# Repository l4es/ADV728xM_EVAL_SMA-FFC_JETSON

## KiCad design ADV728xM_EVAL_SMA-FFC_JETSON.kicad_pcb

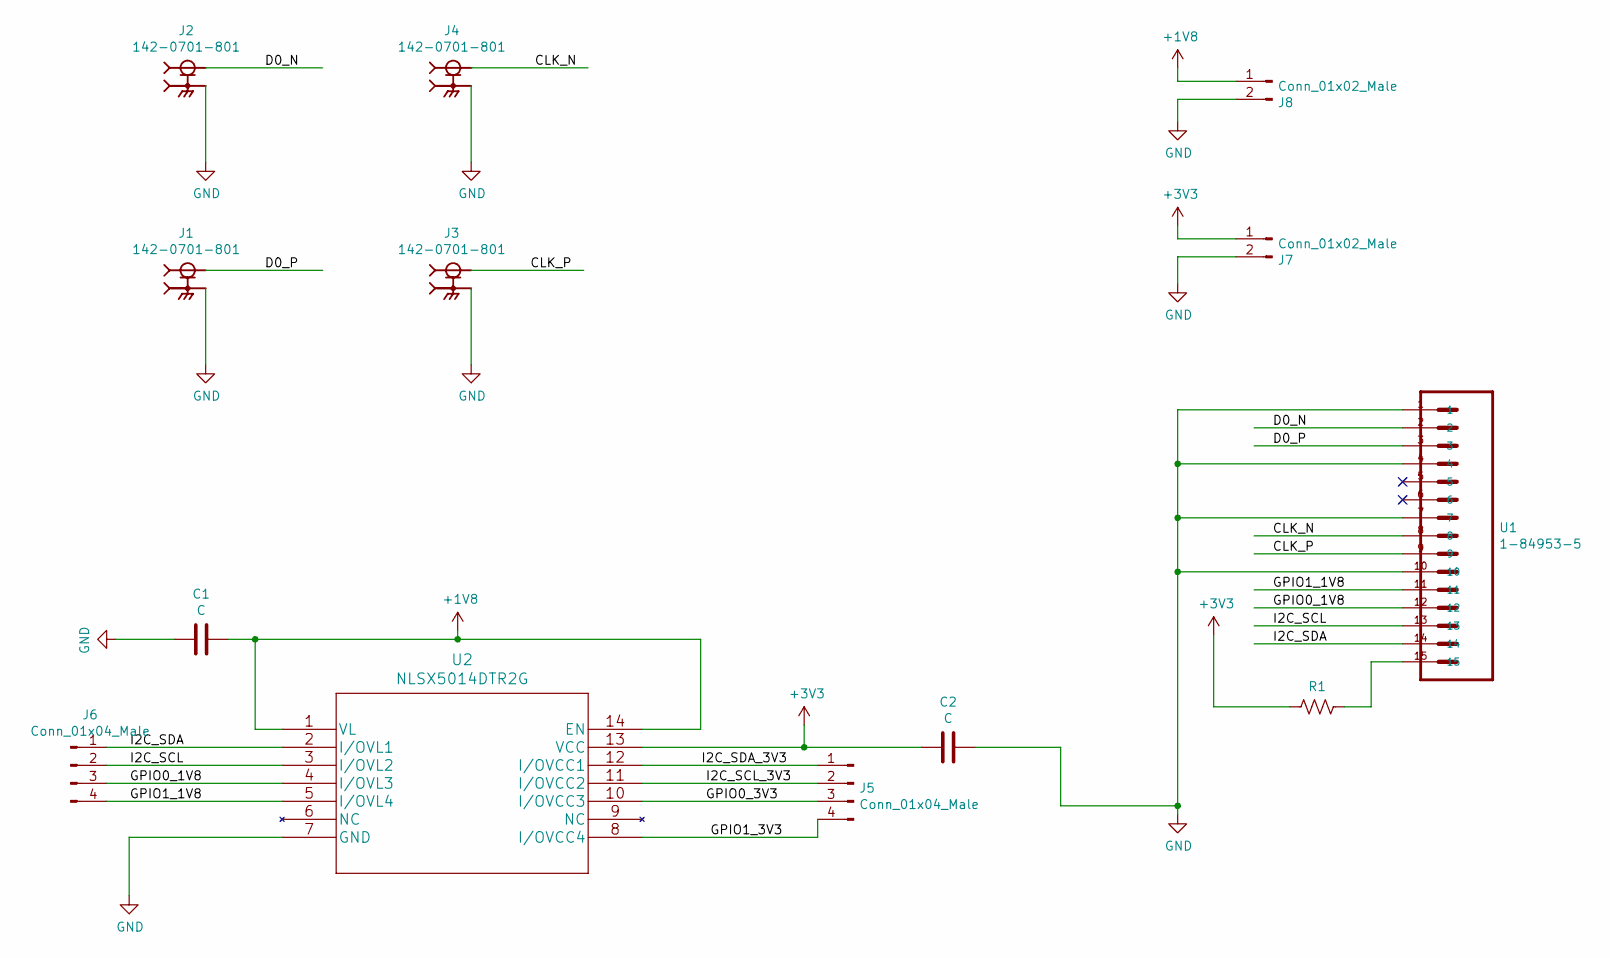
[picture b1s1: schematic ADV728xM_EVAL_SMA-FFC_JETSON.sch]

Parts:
C1, C2: C; C_0603_1608Metric_Pad1.08x0.95mm_HandSolder
J1, J2, J3, J4: 142-0701-801; CINCH_142-0701-801; PARTREV N/A
J5, J6: Conn_01x04_Male; PinHeader_1x04_P2.54mm_Vertical
J7, J8: Conn_01x02_Male; PinHeader_1x02_P2.54mm_Vertical
R1: 0; R_0805_2012Metric_Pad1.20x1.40mm_HandSolder
U1: 1-84953-5; TE_1-84953-5
U2: NLSX5014DTR2G

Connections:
+1V8: C1.2, J8.1, U2.1 (VL), U2.14 (EN)
+3V3: C2.2, J7.1, R1.2, U2.13 (VCC)
/CLK_N: J4.1, U1.8
/CLK_P: J3.1, U1.9
/D0_N: J2.1, U1.2
/D0_P: J1.1, U1.3
/GPIO0_1V8: J6.3, U1.12, U2.4 (I/OVL3)
/GPIO0_3V3: J5.3, U2.10 (I/OVCC3)
/GPIO1_1V8: J6.4, U1.11, U2.5 (I/OVL4)
/GPIO1_3V3: J5.4, U2.8 (I/OVCC4)
/I2C_SCL: J6.2, U1.13, U2.3 (I/OVL2)
/I2C_SCL_3V3: J5.2, U2.11 (I/OVCC2)
/I2C_SDA: J6.1, U1.14, U2.2 (I/OVL1)
/I2C_SDA_3V3: J5.1, U2.12 (I/OVCC1)
GND: C1.1, C2.1, J1.S1, J1.S2, J1.S3, J1.S4, J2.S1, J2.S2, J2.S3, J2.S4, J3.S1, J3.S2, J3.S3, J3.S4, J4.S1, J4.S2, J4.S3, J4.S4, J7.2, J8.2, U1.1, U1.4, U1.7, U1.10, U2.7 (GND)
unnamed: R1.1, U1.15

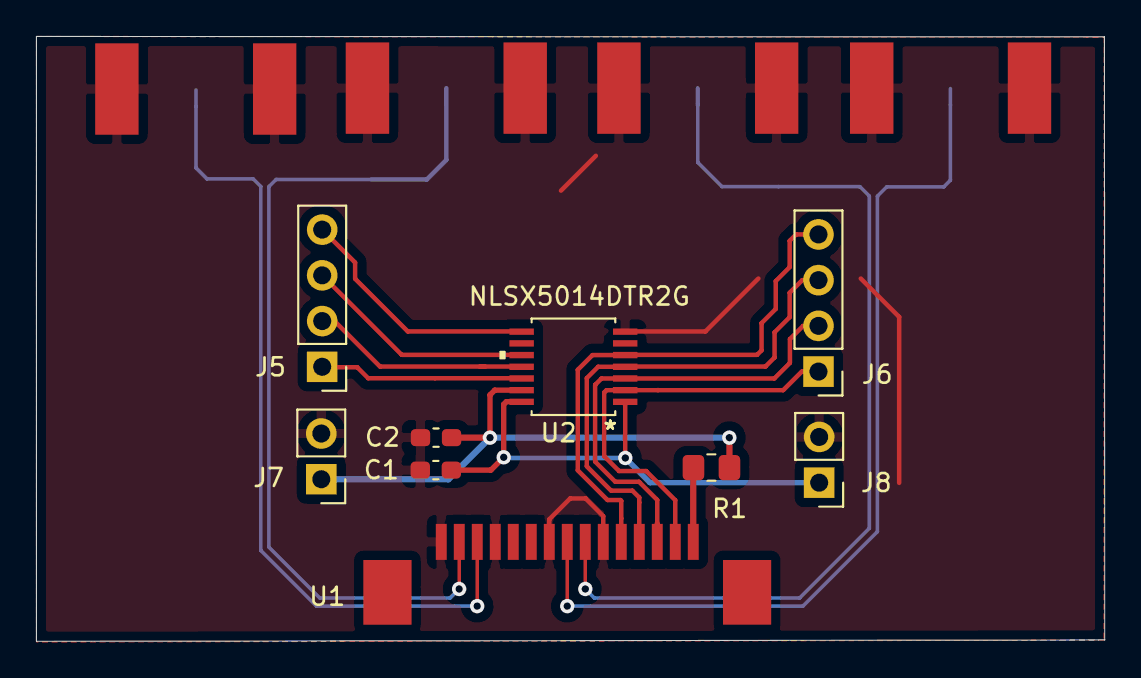
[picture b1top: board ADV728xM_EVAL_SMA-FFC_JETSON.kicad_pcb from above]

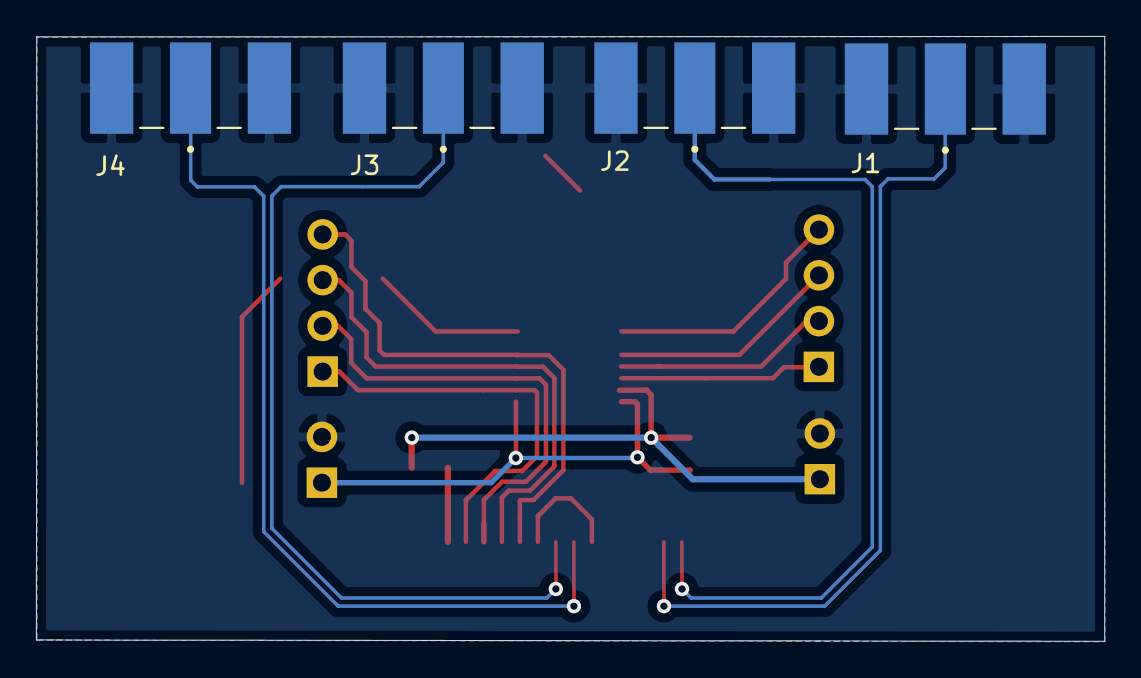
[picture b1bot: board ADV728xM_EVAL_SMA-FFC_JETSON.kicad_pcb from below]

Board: 2 copper layers, 59.3 x 33.6 mm, 13 parts (4 on the bottom side), 16 nets.

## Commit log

2021-07-26 Add production release V1A
2021-08-07 Move SMA connetors to back layer

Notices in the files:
parts and their libraries:
Copyright 2021 Accelerated Designs. All rights reserved.
